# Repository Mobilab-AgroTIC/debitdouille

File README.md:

# Débitdouille

Débitdouille est un système à construire soi-même permettant de suivre les paramètres de pulvérisation en temps réel.

Ces paramètres sont :
- La pression du circuit,
- les débits des sections,
- la vitesse d'avancement.

Tous ces paramètres sont affichés dans la cabine sur le smartphone (Android) du tractoriste via Bluetooth.
Débitdouille a été développé par la CA34 et le mobilab AgroTIC dans le cadre du projet Occitanum. Il est maintenant largement amélioré par Furgo (furgo.fr)

Le [tutoriel d'installation est disponible sur ce lien ](https://mobilab.agrotic.org/2024/11/28/debitdouille/)

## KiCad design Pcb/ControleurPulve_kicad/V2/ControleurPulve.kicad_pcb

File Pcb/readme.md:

# Débitdouille – Électronique

> Gestion de la partie électronique du projet Débitdouille.

---

## 📑 Description

La partie électronique de **Débitdouille** est responsable de :
- L'acquisition de mesures physiques (débit, pression).
- La gestion de l'alimentation.
- La communication avec l'application.

---

## 🖧 Architecture Électronique

```text
+-------------------------------+
|           Capteurs            |
| - 2 x Débitmètres SIKA         |
| - 1 x Capteur de pression      |
+--------------+----------------+
               |
      +--------v--------+
      |  Microcontrôleur  |
      |     ESP32         |
      +--------+--------+
               |
      +--------v--------+
      |   Module de comm  |
      |    (Wi-Fi / BLE)  |
      +------------------+
```
## 📋 Historique des Versions

### [v1.1] - A venir
- Protection contre l'inversion de polarité 12V
- Ajout résistane pullup 
- Ajout ports débitmètres supplémentaires
- Routage : cloutage, largeur de piste 

### [v1.0] - 2025-05-12
- Première version en production.
- Schéma validé.
- Déploiement du PCB v1.
- Tests fonctionnels réalisés.

## 👥 Auteur et contributeurs 

Christophe Auvergne CA34

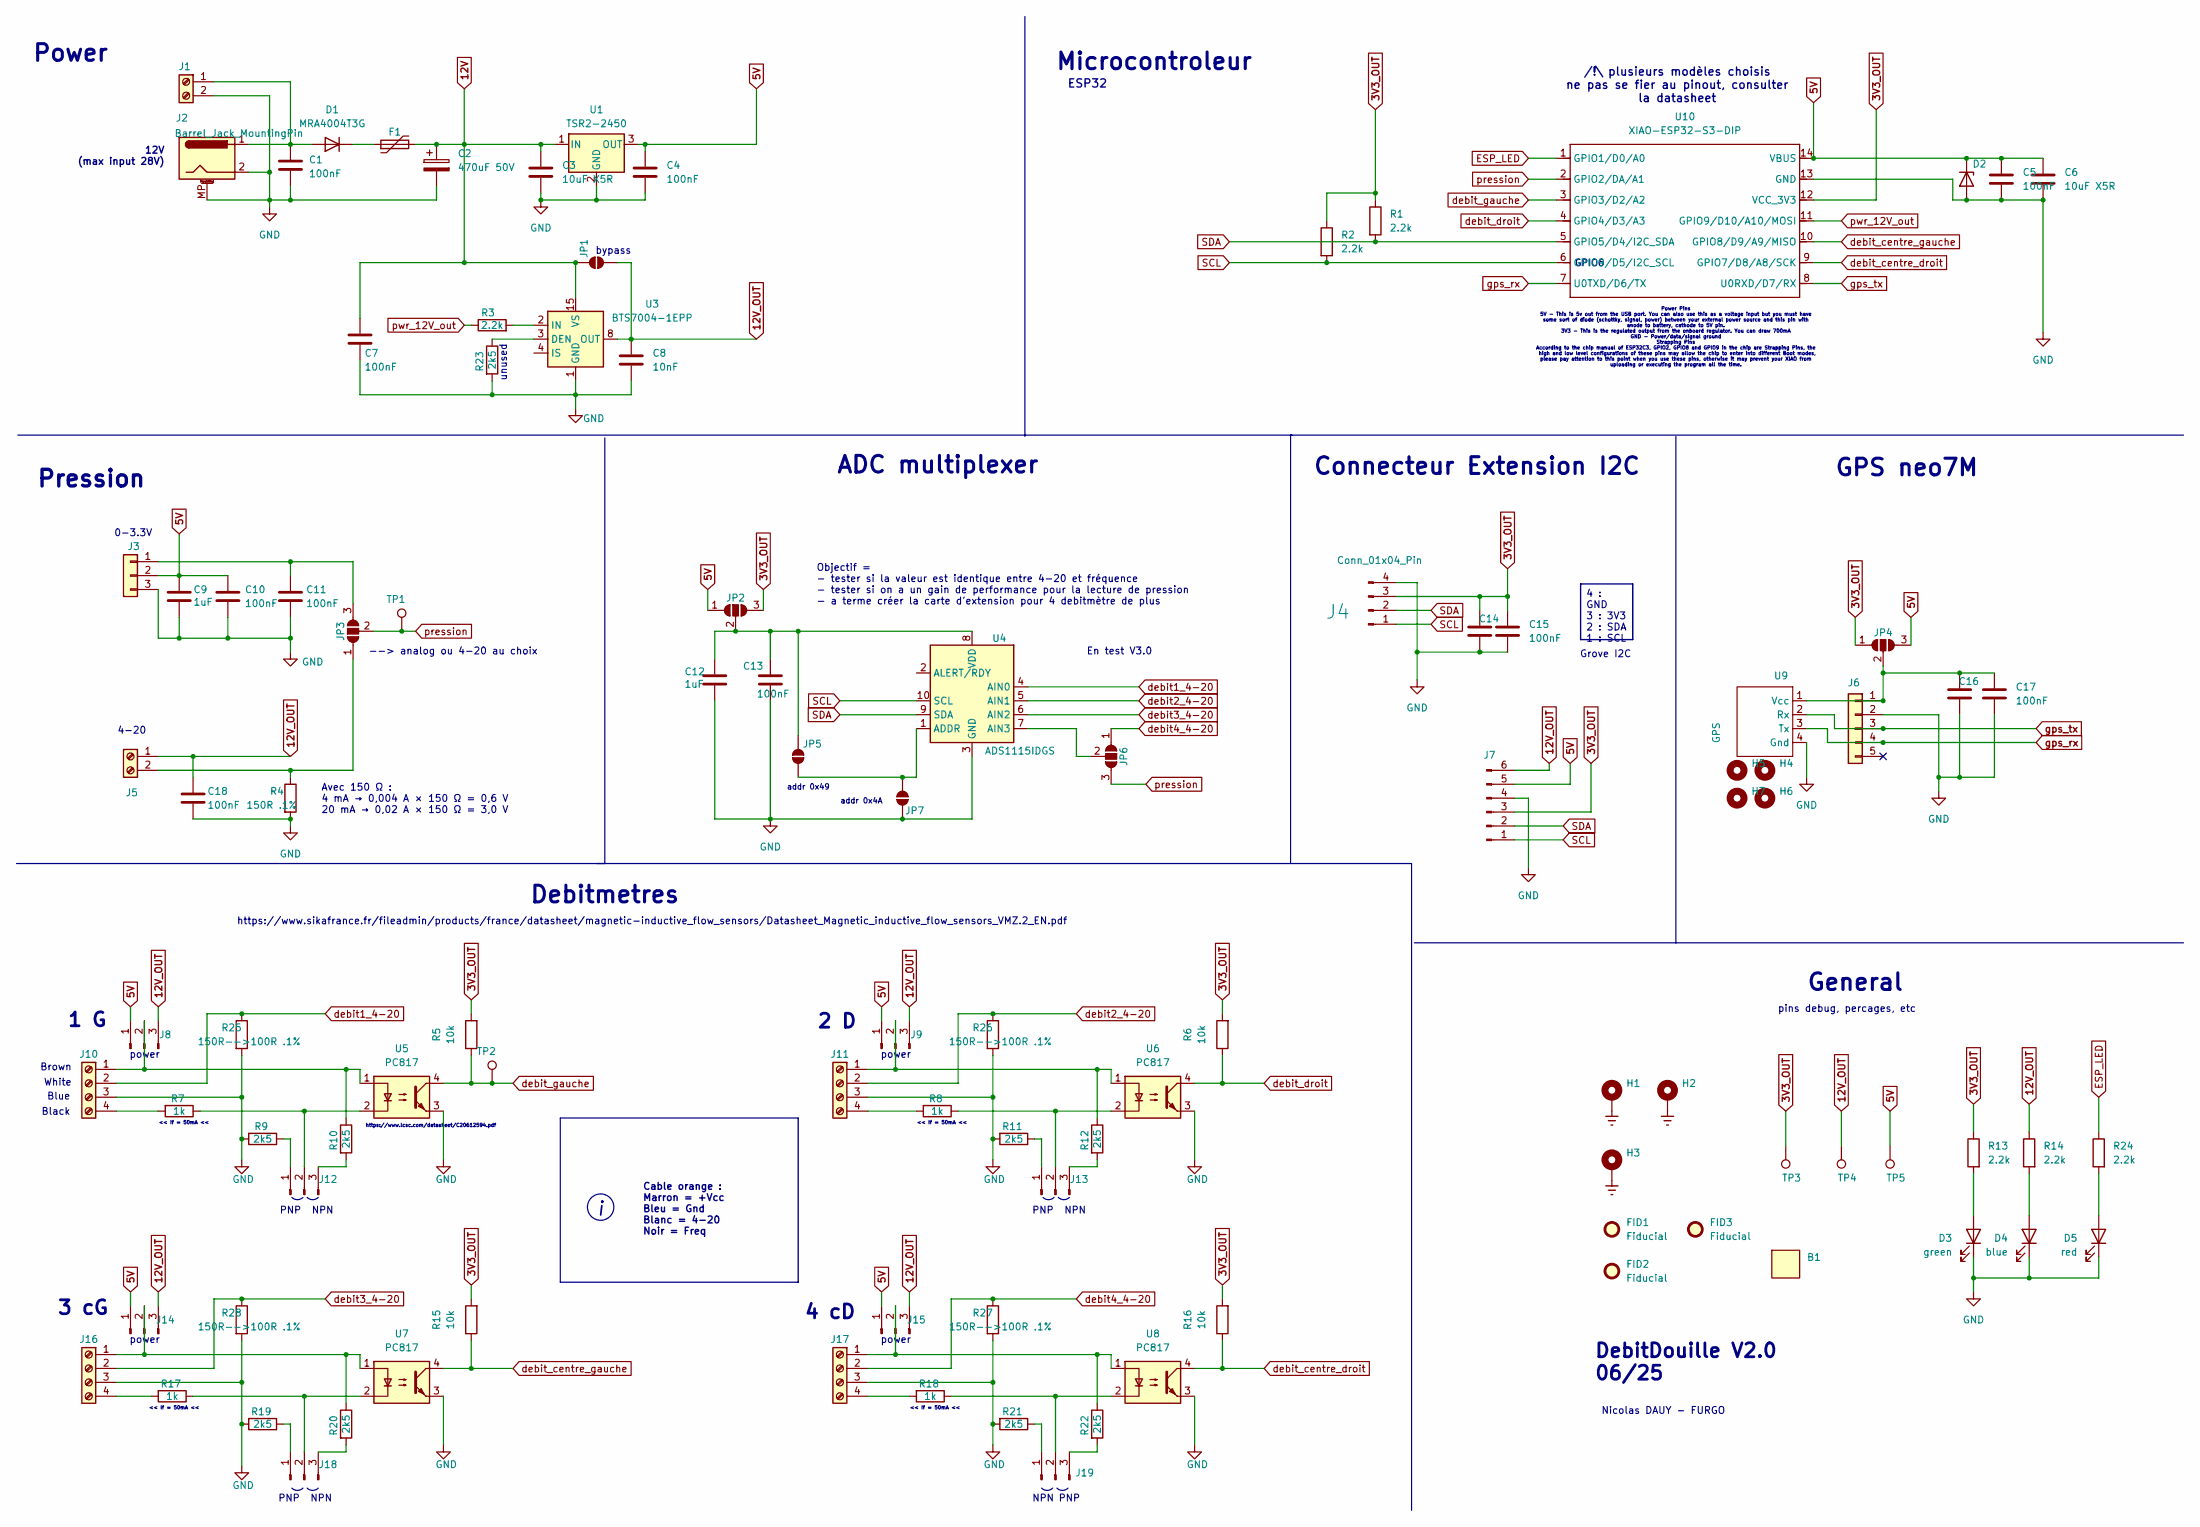
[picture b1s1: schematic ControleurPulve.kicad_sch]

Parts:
B1: EL161_box_enclosure_IDE
C1, C4, C5, C7: 100nF; C_0805_2012Metric; MPN CL10B104KB8NNNC; LCSC C1591
C2: 470uF 50V; CP_Elec_8x10; MPN VP1H221M0810; LCSC C4054388
C3, C6: 10uF X5R; C_0805_2012Metric; MPN CL21A106KBYQNNE; LCSC C2932476
C8: 10nF; C_0603_1608Metric; MPN FCC0603B103K500CT; LCSC C5137477
C9, C12: 1uF; C_0603_1608Metric; MPN CC0603KRX7R9BB104; LCSC C14663
C10, C11, C18: 100nF; C_0603_1608Metric; MPN CL10B104KB8NNNC; LCSC C1591
C13: 100nF; C_0603_1608Metric; MPN CL10B104KB8NNNC; JLCPCB Part C14663
C14, C16: 10uF X5R; C_0603_1608Metric_Pad1.08x0.95mm_HandSolder; MPN CL21A106KBYQNNE; LCSC C2932476
C15, C17: 100nF; C_0603_1608Metric_Pad1.08x0.95mm_HandSolder; MPN CL10B104KB8NNNC; LCSC C1591
D1: MRA4004T3G; D_SMA; MPN MRA4004T3G; LCSC C40324
D2: LESD5D5.0CT1G; D_SOD-523; MPN LESD5D5.0CT1G; LCSC C5199159
D3: green; LED_0603_1608Metric_Pad1.05x0.95mm_HandSolder; MPN YLED0603G; LCSC C19273151
D4: blue; LED_0603_1608Metric_Pad1.05x0.95mm_HandSolder; MPN YLED0603B; LCSC C19171394
D5: red; LED_0603_1608Metric_Pad1.05x0.95mm_HandSolder; MPN YLED0603R; LCSC C19171390
F1: RUILON SMD1812P050TF/30; D_1812_4532Metric_Pad1.30x3.40mm_HandSolder; MPN SMD1812P050TF/30; LCSC C12559
FID1, FID2, FID3: Fiducial; Fiducial_0.5mm_Mask1.5mm
H1, H2, H3: MountingHole_3.2mm_M3_DIN965_Pad; LCSC C3020132
H4, H5, H6, H7: e; MountingHole_3.2mm_M3
J1: Screw_Terminal_01x02; TerminalBlock_Phoenix_MKDS-1,5-2-5.08_1x02_P5.08mm_Horizont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; LCSC C8465
J2: Barrel_Jack_MountingPin; BarrelJack_Horizontal
J3: Analogique 0-3.3V; PinHeader_1x03_P2.54mm_Vertical
J4: Conn_01x04_Pin; JST_PH_S4B-PH-K_1x04_P2.00mm_Horizontal
J5: Screw_Terminal_01x02; TerminalBlock_4Ucon_1x02_P3.50mm_Horizontal; LCSC C784940
J6: GPS; PinSocket_1x05_P2.54mm_Vertical
J7: Conn_01x06_Pin; JST_XH_B6B-XH-A_1x06_P2.50mm_Vertical
J8, J9, J12, J13, J14, J15, J18, J19: Conn_01x03_Pin; PinHeader_1x03_P2.54mm_Vertical; MPN HB-PH3-25413PB2GOP; LCSC C6332196
J10, J11, J16, J17: Screw_Terminal_01x04; TerminalBlock_Phoenix_MKDS-3-4-5.08_1x04_P5.08mm_Horizontal; MPN WJ500V-5.08-4p; LCSC C42377749
JP1: SolderJumper_2_Open; SolderJumper-2_P1.3mm_Open_RoundedPad1.0x1.5mm
JP2, JP3, JP4, JP6: SolderJumper_3_Open; SolderJumper-3_P1.3mm_Open_Pad1.0x1.5mm
JP5, JP7: SolderJumper_2_Open; SolderJumper-2_P1.3mm_Open_TrianglePad1.0x1.5mm
R1, R2, R3, R13, R14, R24: 2.2k; R_0603_1608Metric_Pad0.98x0.95mm_HandSolder; MPN RC0603FR-072K2L; LCSC C114662
R4: 150R .1%; R_0805_2012Metric; MPN PTFR0805B150RN9; LCSC C351609
R5, R6, R15, R16: 10k; R_0603_1608Metric; MPN RC0603FR-0710kL; LCSC C98220
R7, R8, R17, R18: 1k; R_0603_1608Metric; MPN RC0603FR-071kL; LCSC C22548
R9, R10, R11, R12, R19, R20, R21, R22, R23: 2k5; R_0603_1608Metric; MPN AR03BTC2501; LCSC C304065
R25, R26, R27, R28: 150R-->100R .1%; R_0805_2012Metric; MPN PTFR0805B150RN9; LCSC C351609->C328435
TP1, TP2, TP3, TP4, TP5: TestPoint; Pin_D0.7mm_L6.5mm_W1.8mm_FlatFork
U1: TSR2-2450; Converter_DCDC_TRACO_TSR2-xxxx_THT; MPN TSR2-2450; LCSC C5198099
U3: BTS7004-1EPP; Infineon_PG-TSDSO-14-22; MPN BTS7004-1EPP; LCSC C534825
U4: ADS1115IDGS; TSSOP-10_3x3mm_P0.5mm; MPN ADS1115IDGSR; JLCPCB Part C37593
U5, U6, U7, U8: PC817; DIP-4_W8.89mm_SMDSocket_LongPads; MPN PC817CS; LCSC C20612591
U9: GY-NEO6MV2_25_36
U10: XIAO-ESP32-S3-DIP; XIAO-ESP32S3-DIP

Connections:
3V3_OUT: C14.1, C15.1, J4.3, J7.3, JP2.3 (B), JP4.1 (A), R1.1, R2.1, R5.2, R6.2, R13.1, R15.2, R16.2, TP3.1, U10.12 (VCC_3V3); also elsewhere on the board
5V: C4.1, C5.1, C6.1, C9.1, C10.1, D2.1 (K), J3.2, J7.5, J8.1, J9.1, J14.1, J15.1, JP2.1 (A), JP4.3 (B), TP5.1, U1.3 (OUT), U10.14 (VBUS); also elsewhere on the board
12V: C2.1, C3.1, C7.1, F1.2, JP1.2 (B), U1.1 (IN), U3.15 (VS)
12V_OUT: C8.1, C18.1, J5.1, J7.6, J8.3, J9.3, J14.3, J15.3, JP1.1 (A), R14.1, TP4.1, U3.8 (OUT), U3.9 (OUT), U3.10 (OUT), U3.12 (OUT), U3.13 (OUT), U3.14 (OUT)
ESP_LED: R24.1, U10.1 (GPIO1/D0/A0); also elsewhere on the board
GND: C1.2, C2.2, C3.2, C4.2, C5.2, C6.2, C7.2, C8.2, C9.2, C10.2, C11.2, C12.2, C13.2, C14.2, C15.2, C16.2, C17.2, C18.2, D2.2 (A), D3.1 (K), D4.1 (K), D5.1 (K), H1.MP, H2.MP, H3.MP, J1.2, J2.2, J2.MP (MountPin), J3.3, J4.4, J6.2, J7.4, J10.3, J11.3, J16.3, J17.3, JP7.2 (B), R4.2, R9.2, R11.2, R19.2, R21.2, R23.2, R25.2, R26.2, R27.2, R28.2, U1.2 (GND), U3.1 (GND), U4.3 (GND), U5.3, U6.3, U7.3, U8.3, U9.4 (Gnd), U10.13 (GND); also elsewhere on the board
unnamed: C1.1, D1.2 (A), J1.1, J2.1
unnamed: D1.1 (K), F1.1
unnamed: D3.2 (A), R13.2
unnamed: D4.2 (A), R14.2
unnamed: D5.2 (A), R24.2
unnamed: C11.1, J3.1, JP3.3 (B)
unnamed: J5.2, JP3.1 (A), R4.1
unnamed: C16.1, C17.1, J6.1, JP4.2 (C), U9.1 (Vcc)
unnamed: J8.2, J10.1, R10.1, U5.1
unnamed: J10.4, R7.2
unnamed: J9.2, J11.1, R12.1, U6.1
unnamed: J11.4, R8.2
unnamed: J12.1, R9.1
unnamed: J12.2, R7.1, U5.2
unnamed: J12.3, R10.2
unnamed: J13.1, R11.1
unnamed: J13.2, R8.1, U6.2
unnamed: J13.3, R12.2
unnamed: J14.2, J16.1, R20.1, U7.1
unnamed: J15.2, J17.1, R22.1, U8.1
unnamed: J16.4, R17.2
unnamed: J17.4, R18.2
unnamed: J18.1, R19.1
unnamed: J18.2, R17.1, U7.2
unnamed: J18.3, R20.2
unnamed: J19.1, R21.1
unnamed: J19.2, R18.1, U8.2
unnamed: J19.3, R22.2
unnamed: C12.1, C13.1, JP2.2 (C), JP5.2 (B), U4.8 (VDD)
unnamed: JP5.1 (A), JP7.1 (A), U4.1 (ADDR)
unnamed: JP6.2 (C), U4.7 (AIN3)
unnamed: R23.1, U3.3 (DEN)
unnamed: R3.2, U3.2 (IN)
SCL: J4.1, J7.1, R2.2, U4.10 (SCL), U10.6 (GPIO9/D5/I2C_SCL); also elsewhere on the board
SDA: J4.2, J7.2, R1.2, U4.9 (SDA), U10.5 (GPIO5/D4/I2C_SDA); also elsewhere on the board
debit1_4-20: J10.2, R25.1, U4.4 (AIN0)
debit2_4-20: J11.2, R26.1, U4.5 (AIN1)
debit3_4-20: J16.2, R28.1, U4.6 (AIN2)
debit4_4-20: J17.2, JP6.1 (A), R27.1
debit_centre_droit: R16.1, U8.4, U10.9 (GPIO7/D8/A8/SCK); also elsewhere on the board
debit_centre_gauche: R15.1, U7.4, U10.10 (GPIO8/D9/A9/MISO); also elsewhere on the board
debit_droit: R6.1, U6.4, U10.4 (GPIO4/D3/A3); also elsewhere on the board
debit_gauche: R5.1, TP2.1, U5.4, U10.3 (GPIO3/D2/A2); also elsewhere on the board
gps_rx: J6.4, U9.3 (Tx), U10.7 (U0TXD/D6/TX); also elsewhere on the board
gps_tx: J6.3, U9.2 (Rx), U10.8 (U0RXD/D7/RX); also elsewhere on the board
pression: JP3.2 (C), JP6.3 (B), TP1.1, U10.2 (GPIO2/DA/A1); also elsewhere on the board
pwr_12V_out: R3.1, U10.11 (GPIO9/D10/A10/MOSI); also elsewhere on the board

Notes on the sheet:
https://www.lcsc.com/datasheet/C20612594.pdf
Debitmetres
Black
ESP32
unused
White
DebitDouille V2.0 06/25
Power Pins 5V - This is 5v out from the USB port. You can also use this as a voltage input but you must have some sort of diode (schottky, signal, power) between your external power source and this pin with anode to battery, cathode to 5V pin. 3V3 - This is the regulated output from the onboard reg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
PNP
<< If = 50mA <<
GPS neo7M
0-3.3V
addr 0x4A
12V (max input 28V)
Power
pins debug, percages, etc
Connecteur Extension I2C
4 cD
/!\ plusieurs modèles choisis ne pas se fier au pinout, consulter la datasheet
power
ADC multiplexer
Microcontroleur
Avec 150 Ω : 4 mA → 0,004 A × 150 Ω = 0,6 V 20 mA → 0,02 A × 150 Ω = 3,0 V
bypass
En test V3.0
General
2 D
4-20
https://www.sikafrance.fr/fileadmin/products/france/datasheet/magnetic-inductive_flow_sensors/Datasheet_Magnetic_inductive_flow_sensors_VMZ.2_EN.pdf
--> analog ou 4-20 au choix
Brown
3 cG
Nicolas DAUY - FURGO
Objectif = - tester si la valeur est identique entre 4-20 et fréquence - tester si on a un gain de performance pour la lecture de pression - a terme créer la carte d'extension pour 4 debitmètre de plus
Cable orange : Marron = +Vcc Bleu = Gnd Blanc = 4-20 Noir = Freq
GPIO6
NPN
addr 0x49
1 G
Grove I2C

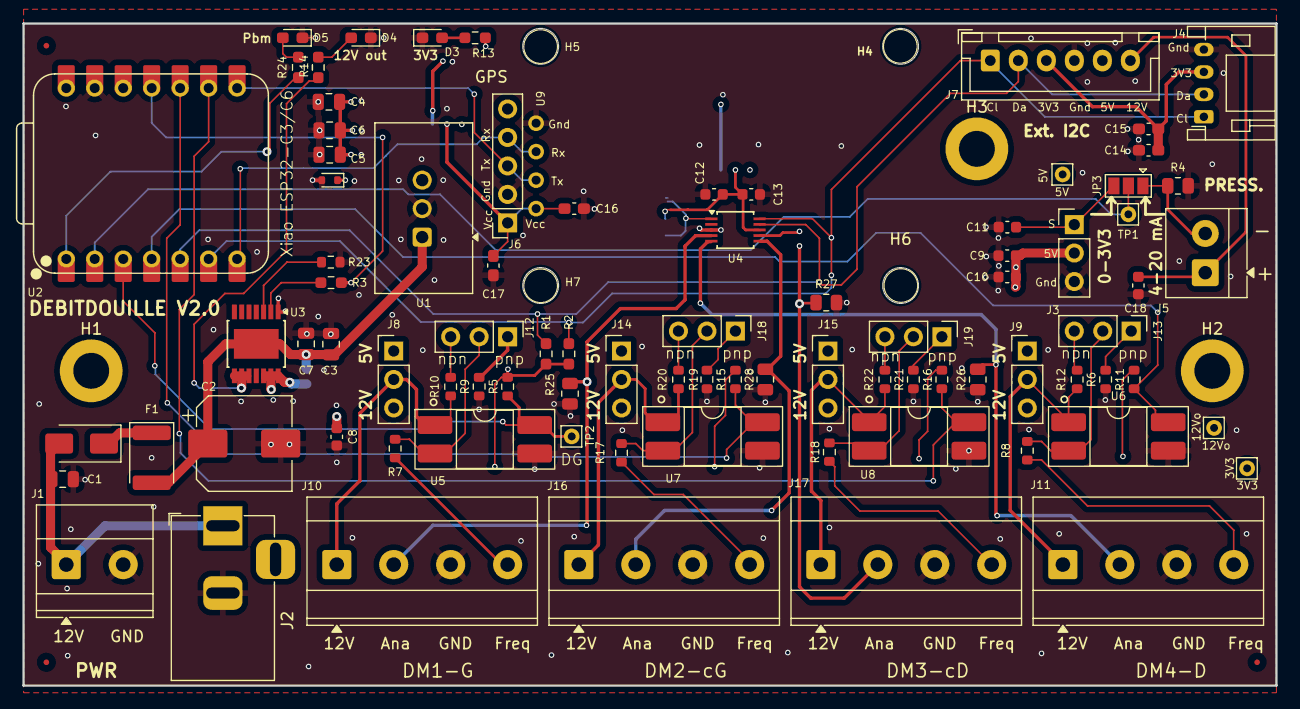
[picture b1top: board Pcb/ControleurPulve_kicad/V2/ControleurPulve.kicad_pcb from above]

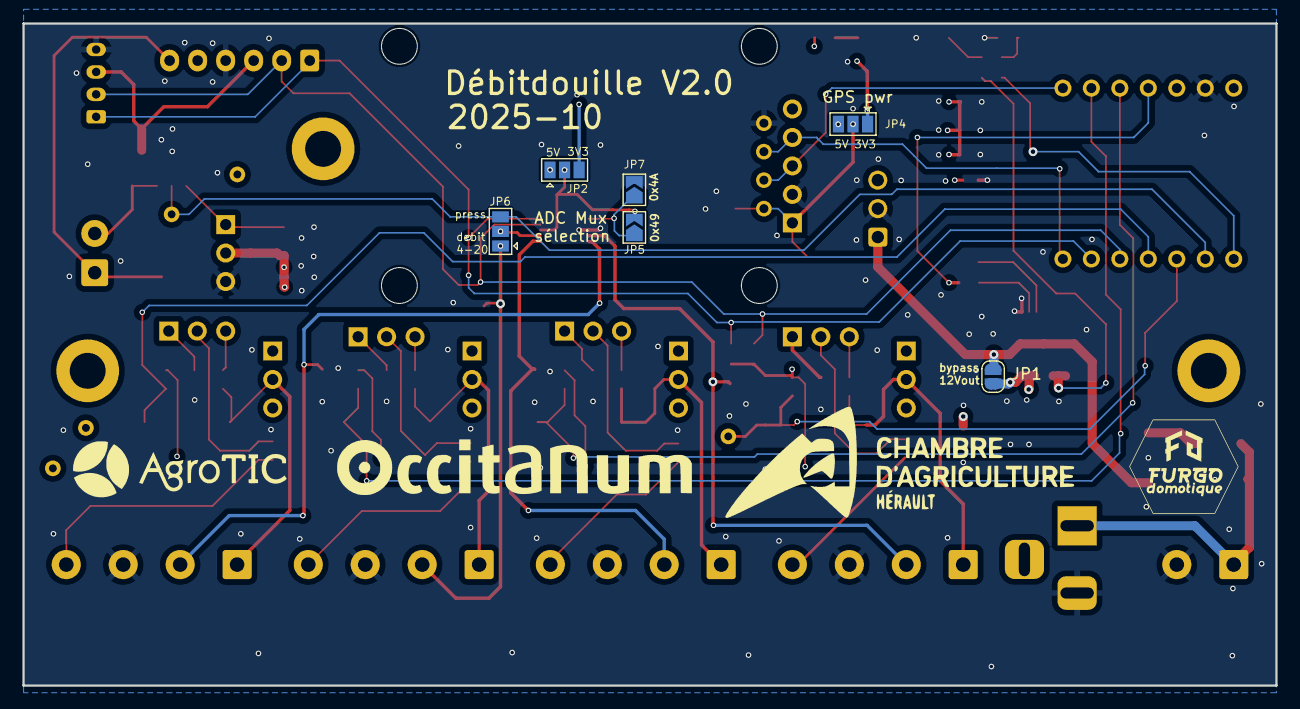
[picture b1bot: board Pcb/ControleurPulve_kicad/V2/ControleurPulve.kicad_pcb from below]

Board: 4 copper layers, 111.8 x 59.1 mm, 103 parts (6 on the bottom side), 53 nets.

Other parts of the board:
U2: XIAO-ESP32-C6; XIAO-ESP32C6-DIP

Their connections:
3V3_OUT: U2.12 (3V3); also elsewhere on the board
5V: U2.14 (VBUS); also elsewhere on the board
ESP_LED: U2.1 (GPIO0/A0/D0); also elsewhere on the board
GND: U2.13 (GND); also elsewhere on the board
SCL: U2.6 (GPIO23/D5/SCL); also elsewhere on the board
SDA: U2.5 (GPIO22/D4/SDA); also elsewhere on the board
debit_centre_droit: U2.9 (GPIO19/D8/SCK); also elsewhere on the board
debit_centre_gauche: U2.10 (GPIO20/D9/MISO); also elsewhere on the board
debit_droit: U2.4 (GPIO21/D3); also elsewhere on the board
debit_gauche: U2.3 (GPIO2/A2/D2); also elsewhere on the board
gps_rx: U2.7 (GPIO16/D6/TX); also elsewhere on the board
gps_tx: U2.8 (GPIO17/D7/RX); also elsewhere on the board
pression: U2.2 (GPIO1/A1/D1); also elsewhere on the board
pwr_12V_out: U2.11 (GPIO18/D10/MOSI); also elsewhere on the board

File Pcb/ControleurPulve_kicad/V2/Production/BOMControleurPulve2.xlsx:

Designator | Comment | Datasheet | Footprint | Qty | DNP | JLCPCB Part | MPN
C1,C4,C5,C7,C10,C11,C13,C15,C17,C18 | 100nF | ~ | Capacitor_SMD:C_0603_1608Metric,Capacitor_SMD:C_0603_1608Metric_Pad1.08x0.95mm_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 | 10 |  | C1591 | CL10B104KB8NNNC
C2 | 470uF 50V | ~ | Capacitor_SMD:CP_Elec_8x10 | 1 |  | C4054388 | VP1H221M0810
C3,C6,C14,C16 | 10uF X5R | ~ | Capacitor_SMD:C_0603_1608Metric_Pad1.08x0.95mm_HandSolder,Capacitor_SMD:C_0805_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 | 4 |  | C2932476 | CL21A106KBYQNNE
C8 | 10nF | ~ | Capacitor_SMD:C_0603_1608Metric | 1 |  | C5137477 | FCC0603B103K500CT
C9,C12 | 1uF | ~ | Capacitor_SMD:C_0603_1608Metric | 2 |  | C14663 | CC0603KRX7R9BB104
D1 | MRA4004T3G | http://www.onsemi.com/pub_link/Collateral/MRA4003T3-D.PDF | Diode_SMD:D_SMA | 1 |  | C40324 | MRA4004T3G
D2 | LESD5D5.0CT1G | https://www.onsemi.com/pdf/datasheet/esd5z2.5t1-d.pdf | Diode_SMD:D_SOD-523 | 1 |  | C5199159 | LESD5D5.0CT1G
D3 | green | ~ | LED_SMD:LED_0603_1608Metric_Pad1.05x0.95mm_HandSolder | 1 |  | C19273151 | YLED0603G
D4 | blue | ~ | LED_SMD:LED_0603_1608Metric_Pad1.05x0.95mm_HandSolder | 1 |  | C19171394 | YLED0603B
D5 | red | ~ | LED_SMD:LED_0603_1608Metric_Pad1.05x0.95mm_HandSolder | 1 |  | C19171390 | YLED0603R
F1 | RUILON SMD1812P050TF/30 | ~ | Diode_SMD:D_1812_4532Metric_Pad1.30x3.40mm_HandSolder | 1 |  | C12559 | SMD1812P050TF/30
J1 | Screw_Terminal_01x02 | ~ | TerminalBlock_Phoenix:TerminalBlock_Phoenix_MKDS-1,5-2-5.08_1x02_P5.08mm_Horizo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 | 1 |  | C8465
J5 | Screw_Terminal_01x02 | ~ | TerminalBlock_4Ucon:TerminalBlock_4Ucon_1x02_P3.50mm_Horizontal | 1 |  | C784940
J8,J9,J12,J13,J14,J15,J18,J19 | Conn_01x03_Pin | ~ | Connector_PinHeader_2.54mm:PinHeader_1x03_P2.54mm_Vertical | 8 |  | C6332196 | HB-PH3-25413PB2GOP
J10,J11,J16,J17 | Screw_Terminal_01x04 | ~ | TerminalBlock_Phoenix:TerminalBlock_Phoenix_MKDS-3-4-5.08_1x04_P5.08mm_Horizont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 | 4 |  | C42377749 | WJ500V-5.08-4p
R1,R2,R3,R13,R14,R24 | 2.2k | ~ | Resistor_SMD:R_0603_1608Metric_Pad0.98x0.95mm_HandSolder | 6 |  | C114662 | RC0603FR-072K2L
R4 | 150R .1% | ~ | Resistor_SMD:R_0805_2012Metric | 1 |  | C351609 | PTFR0805B150RN9
R5,R6,R15,R16 | 10k | ~ | Resistor_SMD:R_0603_1608Metric | 4 |  | C98220 | RC0603FR-0710kL
R7,R8,R17,R18 | 1k | ~ | Resistor_SMD:R_0603_1608Metric | 4 |  | C22548 | RC0603FR-071kL
R9,R10,R11,R12,R19,R20,R21,R22,R23 | 2k5 | ~ | Resistor_SMD:R_0603_1608Metric | 9 |  | C304065 | AR03BTC2501
U1 | TSR2-2450 | https://www.recom-power.com/pdf/Innoline/R-78Exx-0.5.pdf | Converter_DCDC:Converter_DCDC_TRACO_TSR2-xxxx_THT | 1 |  | C5198099 | TSR2-2450
U3 | BTS7004-1EPP | https://www.infineon.com/dgdl/Infineon-BTS7004-1EPP-DS-v01_0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 | Package_SO:Infineon_PG-TSDSO-14-22 | 1 |  | C534825 | BTS7004-1EPP
U4 | ADS1115IDGS | http://www.ti.com/lit/ds/symlink/ads1113.pdf | Package_SO:TSSOP-10_3x3mm_P0.5mm | 1 |  | C37593 | ADS1115IDGSR
U5,U6,U7,U8 | PC817 | http://www.soselectronic.cz/a_info/resource/d/pc817.pdf | Package_DIP:DIP-4_W8.89mm_SMDSocket_LongPads | 4 |  | C20612591 | PC817CS

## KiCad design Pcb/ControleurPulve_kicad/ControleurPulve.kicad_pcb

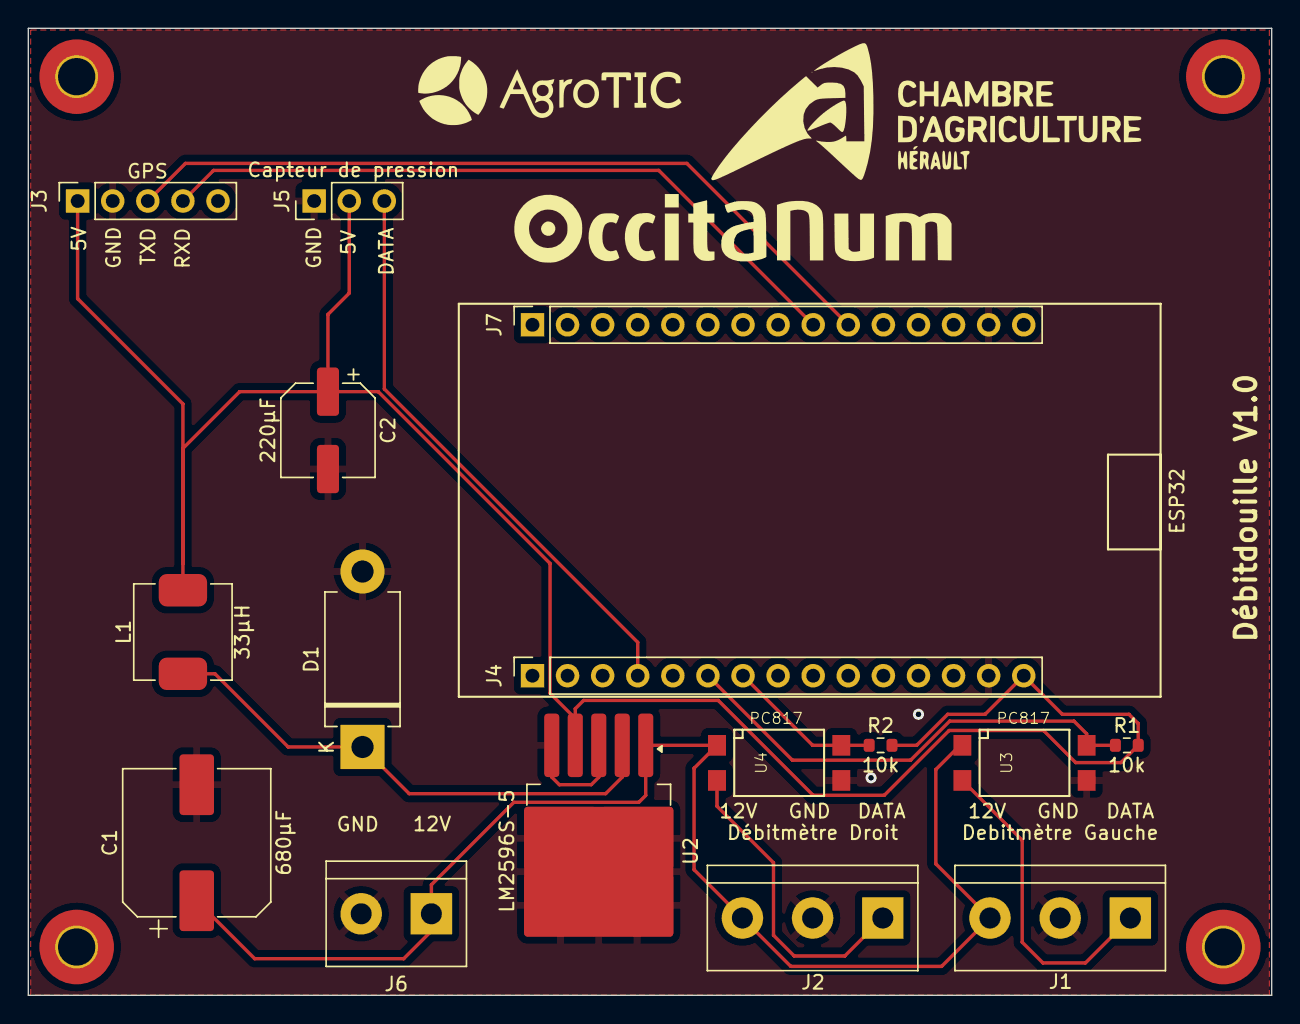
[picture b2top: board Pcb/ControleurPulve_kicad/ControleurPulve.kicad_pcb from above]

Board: 2 copper layers, 90.0 x 70.0 mm, 20 parts (0 on the bottom side), 11 nets.

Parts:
 : MountingHole_2.7mm_M2.5_Pad_TopBottom
 #2,  #3,  #4: MountingHole_2.7mm_M2.5_Pad_TopBottom
C1: 680µF; CP_Elec_10x10.5
C2: 220µF; CP_Elec_6.3x5.4
D1: 1N5821; D_DO-201AD_P12.70mm_Horizontal
J1: Debitmètre Gauche; TerminalBlock_bornier-3_P5.08mm
J2: Débitmètre Droit; TerminalBlock_bornier-3_P5.08mm
J3: GPS; PinSocket_1x05_P2.54mm_Vertical
J4: Conn_G; PinSocket_1x15_P2.54mm_Vertical
J5: Capteur de pression; PinHeader_1x03_P2.54mm_Vertical
J6: 12V; TerminalBlock_bornier-2_P5.08mm
J7: Conn_D; PinSocket_1x15_P2.54mm_Vertical
L1: 33µH; L_Changjiang_FXL0650
R1, R2: 10k; R_0603_1608Metric
U2: LM2596S-5; TO-263-5_TabPin3
U3, U4: PC817; OPTO-SMD4

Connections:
+5V: C2.1, J3.1, J4.15, J5.2, L1.2, R1.2, R2.2, U2.4 (FB)
+12V: C1.1, J1.3, J2.3, J6.1, U2.1 (VIN), U3.1, U4.1
GND: C1.2, C2.2, D1.2 (A), J1.2, J2.2, J3.2, J4.14, J5.1, J6.2, J7.14, U2.3 (GND), U2.5 (~ON/OFF), U3.3, U4.3
unnamed: D1.1 (K), L1.1, U2.2 (OUT)
unnamed: J1.1, U3.2
unnamed: J2.1, U4.2
unnamed: J3.3, J7.10
unnamed: J3.4, J7.9
unnamed: J4.4, J5.3
unnamed: J4.6, R1.1, U3.4
unnamed: J4.7, R2.1, U4.4

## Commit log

2024-04-24 update
    update
2024-06-05 update
    Adapté pour capteur SIKA NPN
2024-06-05 Update PulvePressureGpsFlowBluetooth.ino
    ajout parenthese
2024-06-05 update
    Correction pression
2025-02-05 Rename PulvePressure.apk to debitdouille.apk
2025-03-26 Rename Liste Matériel Débitdouille.xlsx to Liste Matériel Débitdouille.xlsx
2025-03-26 Rename readme.md to readme.md
2025-05-12 Ajout electronique initiale
2025-05-26 code en plusiuers fichiers lecture debitmètre full async
2025-05-27 Changement lecture pression Debitmetres full async Fichier config.h
2025-06-05 Ajout instance flutter
2025-06-05 Fix home page source
2025-06-05 Add BLE scan button
2025-06-06 modify folder
2025-08-21 prepare for flutter version
2025-08-21 Ajout de l'appli V1.0 en flutter
2025-09-01 Avancement schematic
2025-09-14 suppr du test
2025-10-17 Electronique V2 schematic (non routée)
2025-10-19 PCB : silkscreen et placement (non routé)
2025-10-21 Mise en prod
2025-11-04 Dév PCB : en cours de validation PCB reçus Code V2
2025-11-05 App flutter : - reconnexion automatique - scan BLE automatique - verification perte de trame - calibration debitmètres Arduino : - formatage des données envoyées - trame de calibration
2025-11-05 App flutter : calibration pression (2 modèles), calibration debit choix de la source.
2025-11-05 Code arduino V2.1 Code flutter V2.1 Ajout versionning.
2025-11-07 Patch arduino : - mix de namespace dans les préférences NVS (application mauvais modèle capteur pression par défaut) - erreur d'allocation débitmètre droit
2025-11-07 Reset des valeurs à 0 quand il détecte reconnexion en cours
2026-04-05 3D printing supports
2026-04-05 PCNT
2026-04-06 Create git
2026-06-05 feat: précision d'affichage réglable, lissage, gestion erreurs BLE
    Versions
    - App Flutter : 2.0.2+2 (patch)
    - Firmware : patch mapping débitmètre V1 (cible active V2_S3)
    App Flutter
    - Précision d'affichage réglable par grandeur (pression / débits / vitesse), 0 à 3 décimales, défaut 1 décimale
    - Moyenne glissante (fenêtre 5 trames) pour stabiliser l'affichage des valeurs
2026-06-05 Enhance README with project details and updates
    Updated project attribution and added information about improvements.
2026-06-06 fix: affichage fiable de la version de l'app (lue du pubspec + date de build)
    Versions
    - App Flutter : 2.0.2+4
    App Flutter
    - Version affichee lue automatiquement depuis le pubspec via package_info_plus (init au demarrage), au lieu d'une constante codee en dur - supprime tout risque de decalage entre version reelle et ver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
    - Date de compilation injectee au build (--dart-define=BUILD_DATE) et affichee
    - Libelle de l'ecran Parametres : "Version app Flutter : 2.0.2 (build 4) - jj/mm/aaaa hh:mm"
